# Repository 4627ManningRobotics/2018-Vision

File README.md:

How-To-Vision for Team 4627

The Vision processor is a Raspberry Pi3.  It consumes camera streams from the Camera processors which are Raspberry Pi0W's with Pi camera modules (v1.3 and v2.0).

[Vision Architecture](Vision-architecture.odg)

[Camera Processor Installation](Cam.md)

[Vision Processor Installation](Vision.md)

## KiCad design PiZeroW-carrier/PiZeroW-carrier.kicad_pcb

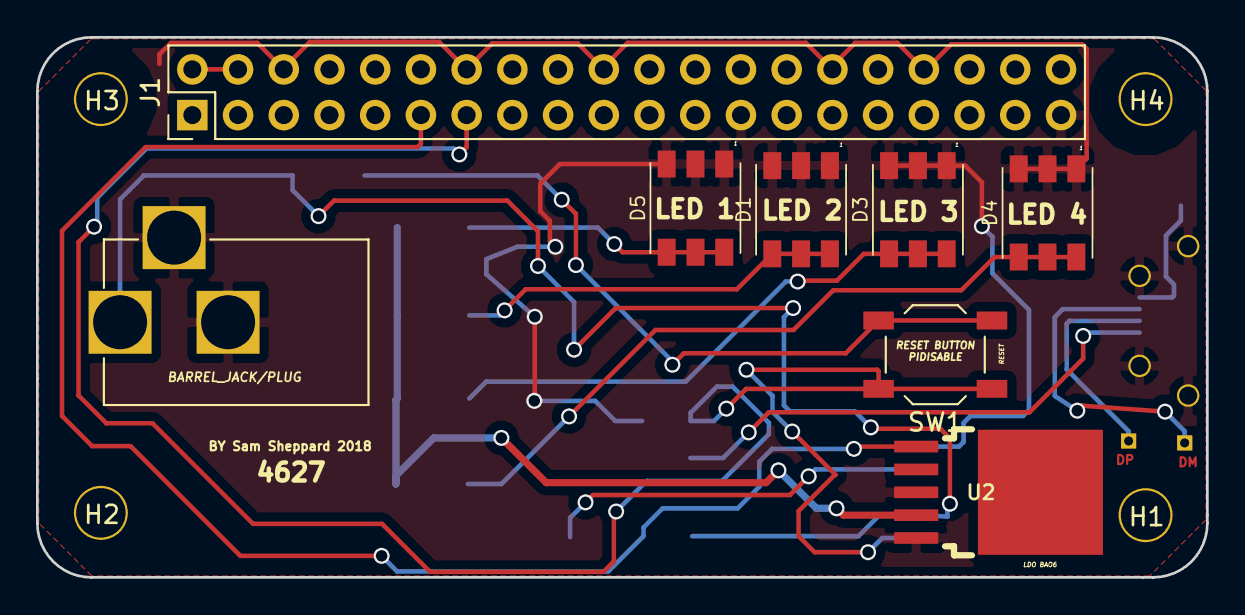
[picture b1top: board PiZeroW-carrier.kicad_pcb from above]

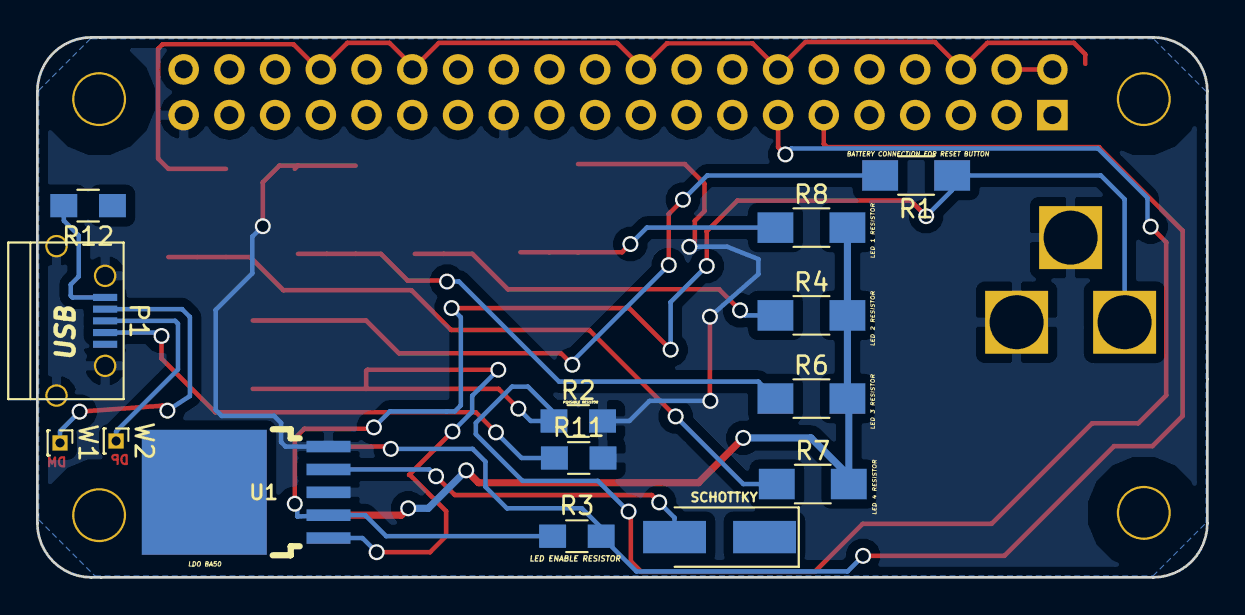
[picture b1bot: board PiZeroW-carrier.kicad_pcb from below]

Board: 2 copper layers, 65.0 x 30.0 mm, 26 parts (14 on the bottom side), 15 nets.

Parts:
CON1: BARREL_JACK
D1, D3, D4, D5: LED_QBLP679E; 5050
D6: D_Schottky; D_SMA_Handsoldering
H1, H2, H3, H4: Hole_3mm_PTH; NPTH_3mm_ID
J1: PI40HAT; Pin_Header_Straight_2x20_Pitch2.54mm
P1: USB_OTG; USB_Micro-B
R1, R4, R6, R7, R8: 150; R_1206_HandSoldering
R2, R3: 10k; R_0805_HandSoldering
R11, R12: DNP; R_0805_HandSoldering
SW1: SW_PUSH; SW_SPST_TL3342
U1: BA50BC0WFP-E2CT; TO-252-5
U2: BA06CC0WFP-E2CT; TO-252-5
W1: D-; Pin_Header_Straight_1x01_Pitch1.00mm
W2: D+; Pin_Header_Straight_1x01_Pitch1.00mm

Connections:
+BATT: CON1.1, R1.1, R3.1, U1.2, U2.2
/Leds/+6V: R4.2, R6.2, R7.2, R8.2, U2.4
/Power/LEDEnable: J1.11, R3.2, U2.1
/Power/PIDisable: J1.13, R2.1, SW1.1, U1.1
/raspberrypi-gpio-40pin/P5V_HAT: J1.2, J1.4
GND: CON1.2, CON1.3, D1.1, D1.2, D1.3, D3.1, D3.2, D3.3, D4.1, D4.2, D4.3, D5.1, D5.2, D5.3, J1.6, J1.9, J1.14, J1.20, J1.25, J1.30, J1.34, J1.39, P1.5, P1.6, R2.2, R11.2, U1.3, U1.5, U2.3, U2.5
unnamed: D1.4, D1.5, D1.6, R4.1
unnamed: D3.4, D3.5, D3.6, R6.1
unnamed: D4.4, D4.5, D4.6, R7.1
unnamed: D5.4, D5.5, D5.6, R8.1
unnamed: D6.2, U1.4
unnamed: P1.1, R12.2
unnamed: P1.2, W1.1
unnamed: P1.3, W2.1
unnamed: P1.4, R11.1

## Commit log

2017-10-27 add mjpg-streamer and binaries
2017-10-27 add a startup script
2017-10-27 some initial instructions. The Team will expand on this
2017-10-28 Updated documentation
    - Added Vision.md instructions for Pi3 main vision processor install.
    - Link README.md to Vision.md
2017-10-28 Add some more pkgs required to get GRIP python code to run
    If we're going to export code to Pythonl, then we need some additional libraries and so forth.
2017-10-30 First attempt at representing flow of data
2017-10-31 add vision architecture diagram
2017-11-01 Some initial planning details for carrier card
2017-11-07 Bring in files from 2017 Vision
2017-11-07 Updated HSV Threshold values for this year (from the 2017 repository) for more specific HSV ranges
2017-11-22 clarify the filename
2017-11-26 update to reflect reality
2017-12-05 Initial import of PiZeroW carrier schematic
2017-12-05 update paths for target
2017-12-05 add footprint for LDO's
2017-12-05 add symbol for LDOs
2017-12-05 load symbol for LDOs
2017-12-05 fix symbol for socket strip
2017-12-05 grab some more symbols and footprints from templates/raspberrrypi_hat
2017-12-05 assign component footprints
2017-12-06 datasheet for LEDs
2017-12-07 localize and update USB Micro footprint to match datasheet. Add more datasheets
2018-01-12 Eclipse
    Grip
2018-01-16 Add mjpeg stream handling to last years code
2018-01-18 Create Code
    Back up
2018-01-19 netlist update and read into pcb
2018-01-25 Complete Pizero Layout
    Finnished pi zero led PCB board
2018-01-26 PI Zero PCB finish 2.
    2nd finished PCB Attempt before reading new netlist
2018-01-26 Before Trace fix of LED AND PIDISABLE
    Push before tracing fix of LEDEnable and PIDisable
2018-01-26 cleanup some routes that the autorouter must have created
2018-01-26 fix PiDisable/LEDEnable. Need to connect them on the root sheet. Extra-duh
2018-01-26 need to repour the ground plane to connect the LED gnds
2018-01-26 route LEDEnable and PiDisable. fix 40pin Gnds
2018-01-26 tricky via placement to link a ground pour that became an island
2018-01-26 Re Arranged PCB with hole for camera.
    PCB re arranged to allow more room for camera and Barrel Jack
2018-01-26 Fix of Copper Pour and Placement of the Barrel Jack
    Fixed the Copper Pour from the last Push and Re positioned the Barrel Jack
2018-01-27 Updated Camera Hole Size and moved barrel jack
    Update of the Hole for the camera and placement of the Barrel Jack
2018-01-27 this could work
2018-01-27 fix zone outlines and repour
2018-01-29 Github Made Me push this PCB
    Github made me push this version before i switch branches.
2018-01-29 Layout Change
    Layout Change #2
2018-01-29 Push For alternate
    Push For Alternate
2018-01-29 fix conflicts.
2018-01-29 fixed libs in 2017 code and fixed errors
2018-01-30 Push of (Hopefully) Finnished board
    Need silkscreen stuff
2018-01-30 PCb Now with PIDisable and 6V Connection.
    Featuring a PCB With proper PIDisable and 6V Connections
2018-01-30 SILKS START.
    Start of the silks mdude
2018-01-30 Most(Possibly All Silks)
    Most of ( or maybe all silks????? added to the board!.
2018-01-30 FINISHED BOARD
    Finished Board Yeet
2018-01-31 This one has all the files including both drill files. This is what was sent to AP-Circuits
2018-02-06 pre-rototill checkin
2018-02-13 merged all code
2018-03-07 little fixes
    Little fixes to the code to help compile
